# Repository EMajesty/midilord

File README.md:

# midilord

MIDI controller pedal built on ESP32-S3.

## Hardware

- 8 footswitches
- 4×40 character LCD (ST7066U, 4-bit parallel)
- 1 MIDI IN, multiple MIDI OUTs
- USB MIDI (native ESP32-S3 USB OTG port)
- 9V pedal power, regulated to 5V and 3.3V logic

### LCD pinout (XNY4004A, 18-pin)

| Pin | Function |
|-----|----------|
| 1 | DB0 |
| 2 | DB1 |
| 3 | DB2 |
| 4 | DB3 |
| 5 | DB4 |
| 6 | DB5 |
| 7 | DB6 |
| 8 | DB7 |
| 9 | E1 |
| 10 | R/W |
| 11 | RS |
| 12 | Vo (contrast) |
| 13 | VSS (GND) |
| 14 | VDD (+5V) |
| 15 | E2 |
| 16 | NC |
| 17 | Backlight + |
| 18 | Backlight - |

## Planned features

- Morningstar-inspired function set
- Presets and banks (16 banks × 8 presets)
- Tap tempo
- Web server for preset and config editing

[LCD Datasheet](https://www.crystalfontz.com/products/document/931/CFAH4004A-YYH-JTDatasheetRelease2021-11-03.pdf)
[APA106](https://cdn.sparkfun.com/datasheets/Components/LED/COM-12877.pdf)

```
x0123456789012345678901234567890123456789
0 [Preset]  [Preset]  [Preset]  [Preset]
1
2
3 [Preset]  [Preset]  [Preset]  [Preset]
```

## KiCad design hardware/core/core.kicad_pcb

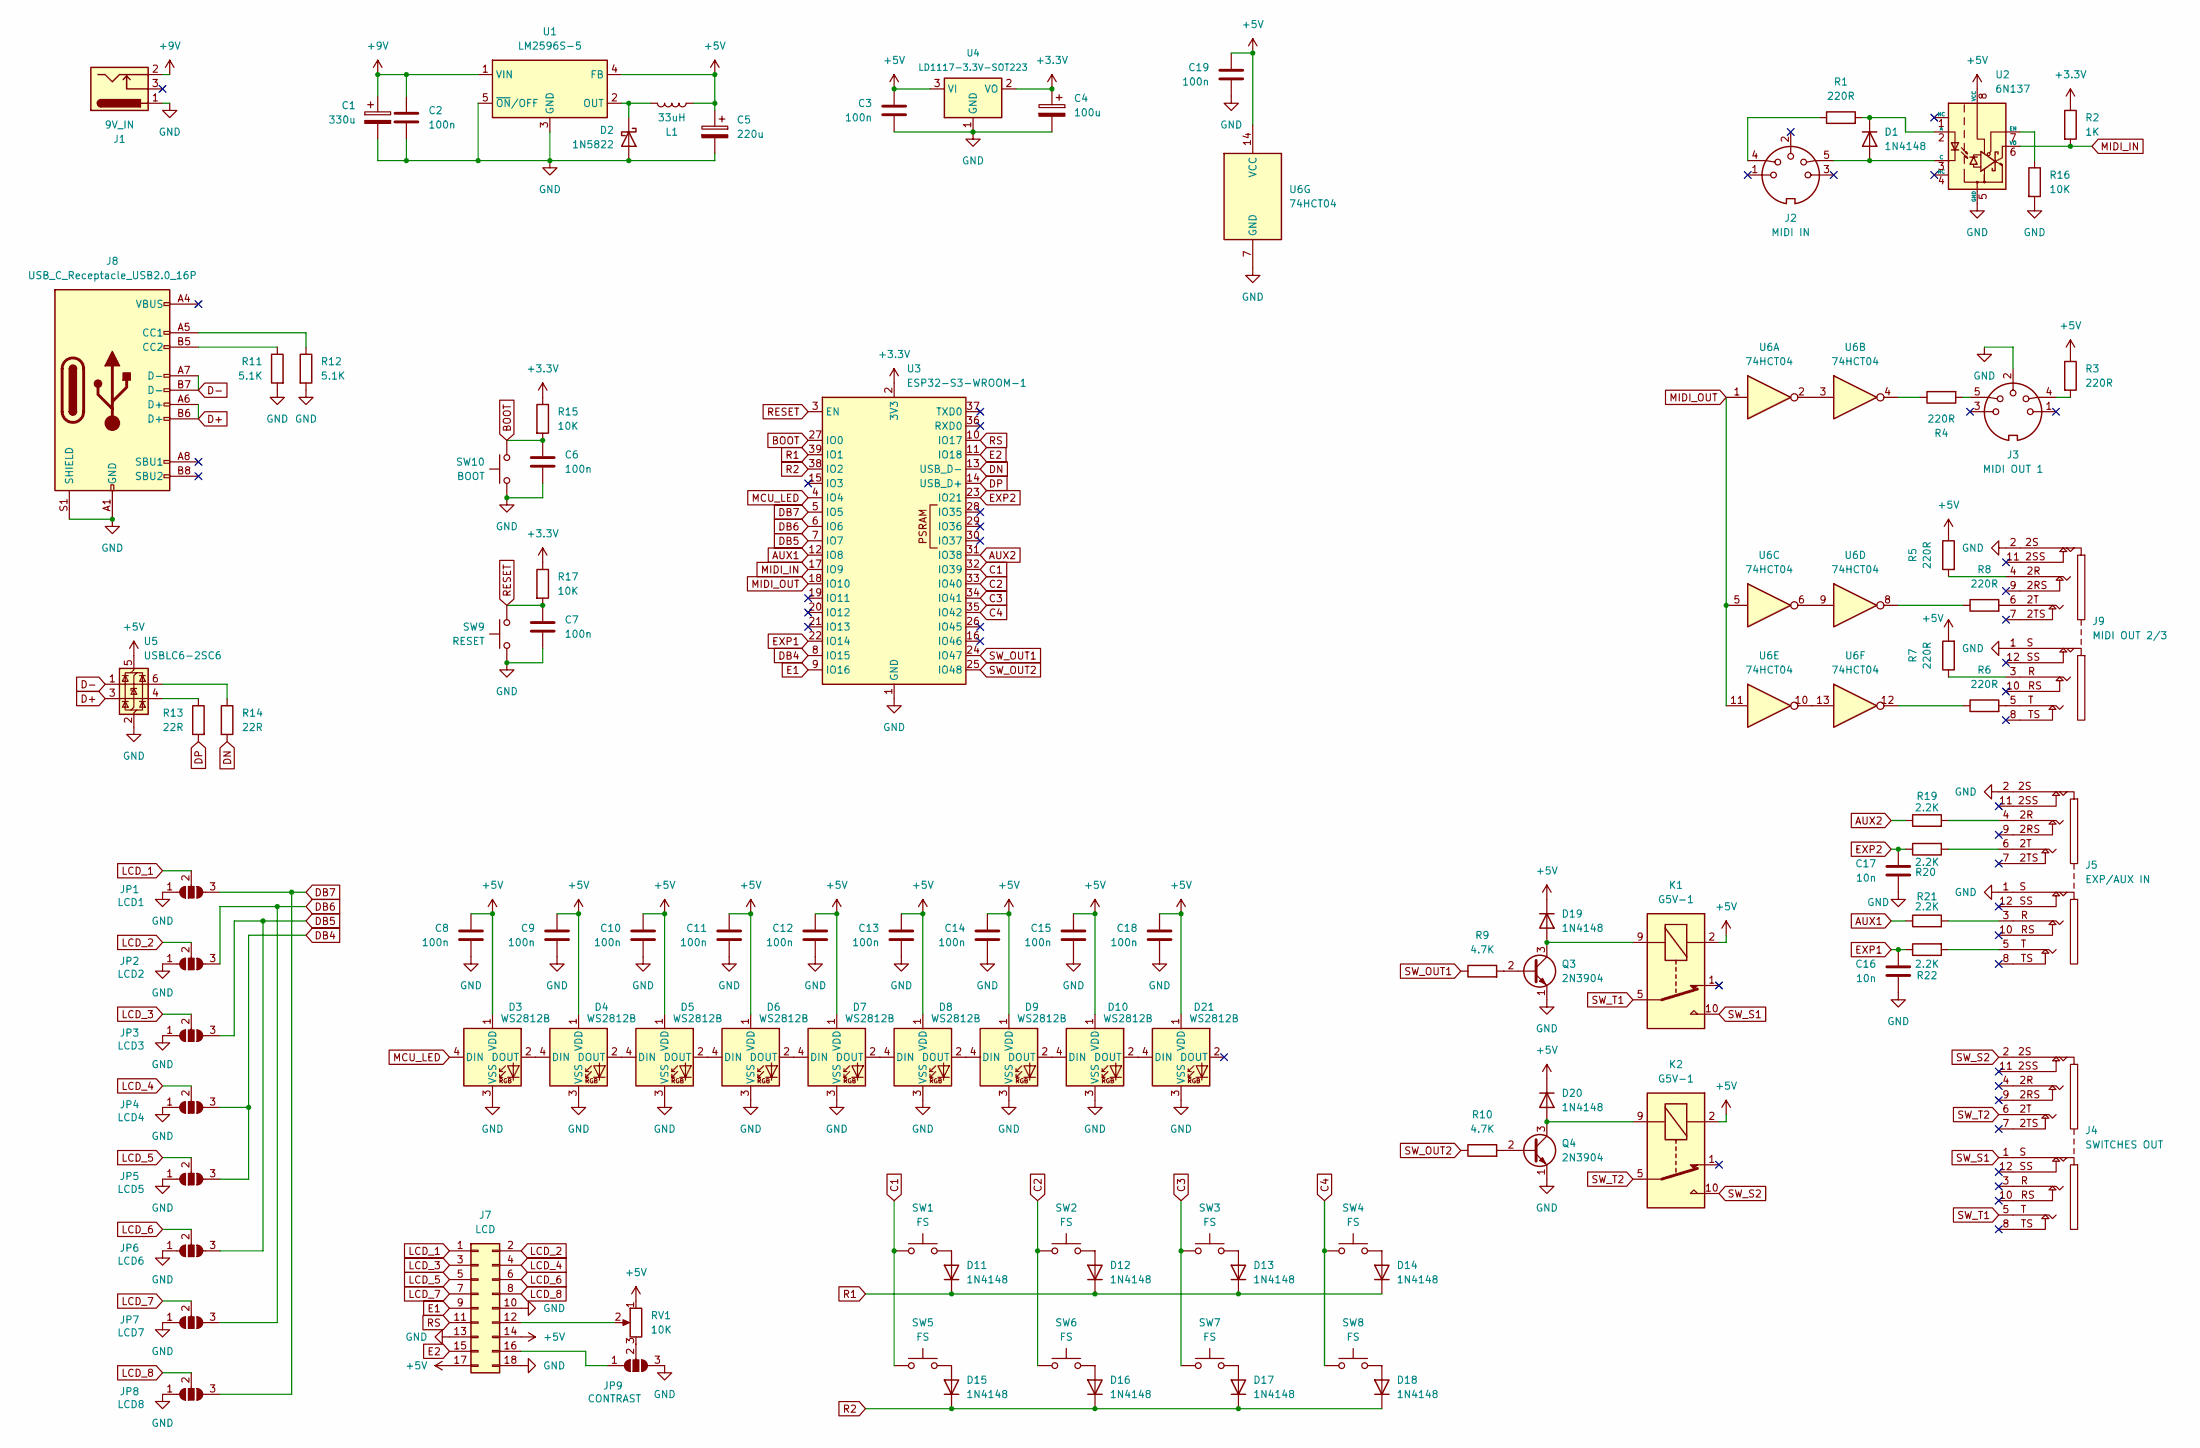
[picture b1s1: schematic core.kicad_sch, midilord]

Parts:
C1: 330u; CP_Radial_D10.0mm_P5.00mm
C2, C3, C6, C7, C8, C9, C10, C11, C12, C13, C14, C15, C18, C19: 100n; C_Rect_L7.0mm_W2.5mm_P5.00mm
C4: 100u; CP_Radial_D8.0mm_P3.50mm
C5: 220u; CP_Radial_D8.0mm_P3.50mm
C16, C17: 10n; C_Rect_L7.0mm_W2.5mm_P5.00mm
D1: 1N4148; D_DO-35_SOD27_P7.62mm_Horizontal
D2: 1N5822; D_DO-201AD_P15.24mm_Horizontal
D3, D4, D5, D6, D7, D8, D9, D10, D21: WS2812B; APA106
D11, D12, D13, D14, D15, D16, D17, D18, D19, D20: 1N4148; D_T-1_P5.08mm_Horizontal
J1: 9V_IN; BarrelJack_Horizontal
J2: MIDI IN; DIN5_180
J3: MIDI OUT 1; DIN5_180
J4: SWITCHES OUT; CK635-037
J5: EXP/AUX IN; CK635-037
J7: LCD; 4004A
J8: USB_C_Receptacle_USB2.0_16P; USB_C_Receptacle_GCT_USB4085
J9: MIDI OUT 2/3; CK635-037
JP1: LCD1; SolderJumper-3_P1.3mm_Open_RoundedPad1.0x1.5mm
JP2: LCD2; SolderJumper-3_P1.3mm_Open_RoundedPad1.0x1.5mm
JP3: LCD3; SolderJumper-3_P1.3mm_Open_RoundedPad1.0x1.5mm
JP4: LCD4; SolderJumper-3_P1.3mm_Open_RoundedPad1.0x1.5mm
JP5: LCD5; SolderJumper-3_P1.3mm_Open_RoundedPad1.0x1.5mm
JP6: LCD6; SolderJumper-3_P1.3mm_Open_RoundedPad1.0x1.5mm
JP7: LCD7; SolderJumper-3_P1.3mm_Open_RoundedPad1.0x1.5mm
JP8: LCD8; SolderJumper-3_P1.3mm_Open_RoundedPad1.0x1.5mm
JP9: CONTRAST; SolderJumper-3_P1.3mm_Open_RoundedPad1.0x1.5mm
K1, K2: G5V-1; Relay_SPDT_Omron_G5V-1
L1: 33uH; L_Radial_D9.5mm_P5.00mm_Fastron_07HVP
Q3, Q4: 2N3904; TO-92_Inline_Wide
R1, R3, R4, R5, R6, R7, R8: 220R; R_Axial_DIN0204_L3.6mm_D1.6mm_P7.62mm_Horizontal
R2: 1K; R_Axial_DIN0204_L3.6mm_D1.6mm_P7.62mm_Horizontal
R9, R10: 4.7K; R_Axial_DIN0204_L3.6mm_D1.6mm_P7.62mm_Horizontal
R11, R12: 5.1K; R_Axial_DIN0204_L3.6mm_D1.6mm_P7.62mm_Horizontal
R13, R14: 22R; R_Axial_DIN0204_L3.6mm_D1.6mm_P7.62mm_Horizontal
R15, R16, R17: 10K; R_Axial_DIN0204_L3.6mm_D1.6mm_P7.62mm_Horizontal
R19, R20, R21, R22: 2.2K; R_Axial_DIN0204_L3.6mm_D1.6mm_P7.62mm_Horizontal
RV1: 10K; Potentiometer_Bourns_3296Y_Vertical
SW1, SW2, SW3, SW4, SW5, SW6, SW7, SW8: FS; Footswitch
SW9: RESET; SW_PUSH_1P1T_6x3.5mm_H5.0_APEM_MJTP1250
SW10: BOOT; SW_PUSH_1P1T_6x3.5mm_H5.0_APEM_MJTP1250
U1: LM2596S-5; TO-263-5_TabPin3
U2: 6N137; DIP-8_W7.62mm
U3: ESP32-S3-WROOM-1
U4: LD1117-3.3V-SOT223; SOT-223; Part Number LD1117S33CTR
U5: USBLC6-2SC6; SOT-23-6
U6: 74HCT04; DIP-14_W7.62mm_Socket_LongPads

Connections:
+3.3V: C4.1, R2.1, R15.1, R17.1, U3.2 (3V3), U4.2 (VO)
+5V: C3.1, C5.1, C8.1, C9.1, C10.1, C11.1, C12.1, C13.1, C14.1, C15.1, C18.1, C19.1, D3.1 (VDD), D4.1 (VDD), D5.1 (VDD), D6.1 (VDD), D7.1 (VDD), D8.1 (VDD), D9.1 (VDD), D10.1 (VDD), D19.1 (K), D20.1 (K), D21.1 (VDD), J7.14, J7.17, K1.2, K2.2, L1.2, R3.1, R5.1, R7.2, RV1.1, U1.4 (FB), U2.8 (VCC), U4.3 (VI), U5.5 (VBUS), U6.14 (VCC)
+9V: C1.1, C2.1, J1.2, U1.1 (VIN)
AUX1: R21.1, U3.12 (IO8)
AUX2: R19.1, U3.31 (IO38)
BOOT: C6.1, R15.2, SW10.2, U3.27 (IO0)
C1: SW1.2, SW5.1, U3.32 (IO39)
C2: SW2.2, SW6.1, U3.33 (IO40)
C3: SW3.1, SW7.2, U3.34 (IO41)
C4: SW4.1, SW8.2, U3.35 (IO42)
D+: J8.A6 (D+), J8.B6 (D+), U5.3 (I/O2)
D-: J8.A7 (D-), J8.B7 (D-), U5.1 (I/O1)
DB4: JP4.3 (B), JP5.3 (B), U3.8 (IO15)
DB5: JP3.3 (B), JP6.3 (B), U3.7 (IO7)
DB6: JP2.3 (B), JP7.3 (B), U3.6 (IO6)
DB7: JP1.3 (B), JP8.3 (B), U3.5 (IO5)
DN: R14.2, U3.13 (USB_D-)
DP: R13.2, U3.14 (USB_D+)
E1: J7.9, U3.9 (IO16)
E2: J7.15, U3.11 (IO18)
EXP1: C16.1, R22.1, U3.22 (IO14)
EXP2: C17.1, R20.1, U3.23 (IO21)
GND: C1.2, C2.2, C3.2, C4.2, C5.2, C6.2, C7.2, C8.2, C9.2, C10.2, C11.2, C12.2, C13.2, C14.2, C15.2, C16.2, C17.2, C18.2, C19.2, D2.2 (A), D3.3 (VSS), D4.3 (VSS), D5.3 (VSS), D6.3 (VSS), D7.3 (VSS), D8.3 (VSS), D9.3 (VSS), D10.3 (VSS), D21.3 (VSS), J1.1, J3.2, J5.1 (S), J5.2 (2S), J7.10, J7.13, J7.18, J8.A1 (GND), J8.A12 (GND), J8.B1 (GND), J8.B12 (GND), J8.S1 (SHIELD), J9.1 (S), J9.2 (2S), JP1.1 (A), JP2.1 (A), JP3.1 (A), JP4.1 (A), JP5.1 (A), JP6.1 (A), JP7.1 (A), JP8.1 (A), JP9.3 (B), Q3.1 (E), Q4.1 (E), R11.2, R12.2, R16.2, SW9.1, SW10.1, U1.3 (GND), U1.5 (~ON/OFF), U2.5 (GND), U3.1 (GND), U3.40 (GND), U3.41 (GND), U4.1 (GND), U5.2 (GND), U6.7 (GND)
LCD_1: J7.1, JP1.2 (C)
LCD_2: J7.2, JP2.2 (C)
LCD_3: J7.3, JP3.2 (C)
LCD_4: J7.4, JP4.2 (C)
LCD_5: J7.5, JP5.2 (C)
LCD_6: J7.6, JP6.2 (C)
LCD_7: J7.7, JP7.2 (C)
LCD_8: J7.8, JP8.2 (C)
MCU_LED: D3.4 (DIN), U3.4 (IO4)
MIDI_IN: R2.2, U2.6 (VO), U3.17 (IO9)
MIDI_OUT: U3.18 (IO10), U6.1, U6.5, U6.11
unnamed: D1.2 (A), J2.5, U2.3 (C)
unnamed: D1.1 (K), R1.2, U2.2 (A)
unnamed: D2.1 (K), L1.1, U1.2 (OUT)
unnamed: D3.2 (DOUT), D4.4 (DIN)
unnamed: D4.2 (DOUT), D5.4 (DIN)
unnamed: D5.2 (DOUT), D6.4 (DIN)
unnamed: D6.2 (DOUT), D7.4 (DIN)
unnamed: D7.2 (DOUT), D8.4 (DIN)
unnamed: D8.2 (DOUT), D9.4 (DIN)
unnamed: D9.2 (DOUT), D10.4 (DIN)
unnamed: D10.2 (DOUT), D21.4 (DIN)
unnamed: D11.2 (A), SW1.1
unnamed: D12.2 (A), SW2.1
unnamed: D13.2 (A), SW3.2
unnamed: D14.2 (A), SW4.2
unnamed: D15.2 (A), SW5.2
unnamed: D16.2 (A), SW6.2
unnamed: D17.2 (A), SW7.1
unnamed: D18.2 (A), SW8.1
unnamed: D19.2 (A), K1.9, Q3.3 (C)
unnamed: D20.2 (A), K2.9, Q4.3 (C)
unnamed: J2.4, R1.1
unnamed: J3.4, R3.2
unnamed: J3.5, R4.2
unnamed: J5.4 (2R), R19.2
unnamed: J5.6 (2T), R20.2
unnamed: J5.3 (R), R21.2
unnamed: J5.5 (T), R22.2
unnamed: J7.12, RV1.2
unnamed: J7.16, JP9.1 (A)
unnamed: J8.A5 (CC1), R12.1
unnamed: J8.B5 (CC2), R11.1
unnamed: J9.4 (2R), R5.2
unnamed: J9.6 (2T), R8.2
unnamed: J9.3 (R), R7.1
unnamed: J9.5 (T), R6.2
unnamed: JP9.2 (C), RV1.3
unnamed: Q3.2 (B), R9.2
unnamed: Q4.2 (B), R10.2
unnamed: R4.1, U6.4
unnamed: R6.1, U6.12
unnamed: R8.1, U6.8
unnamed: R13.1, U5.4 (I/O2)
unnamed: R14.1, U5.6 (I/O1)
unnamed: R16.1, U2.7 (EN)
unnamed: U6.2, U6.3
unnamed: U6.6, U6.9
unnamed: U6.10, U6.13
R1: D11.1 (K), D12.1 (K), D13.1 (K), D14.1 (K), U3.39 (IO1)
R2: D15.1 (K), D16.1 (K), D17.1 (K), D18.1 (K), U3.38 (IO2)
RESET: C7.1, R17.2, SW9.2, U3.3 (EN)
RS: J7.11, U3.10 (IO17)
SW_OUT1: R9.1, U3.24 (IO47)
SW_OUT2: R10.1, U3.25 (IO48)
SW_S1: J4.1 (S), K1.10
SW_S2: J4.2 (2S), K2.10
SW_T1: J4.5 (T), K1.5, K1.6
SW_T2: J4.6 (2T), K2.5, K2.6

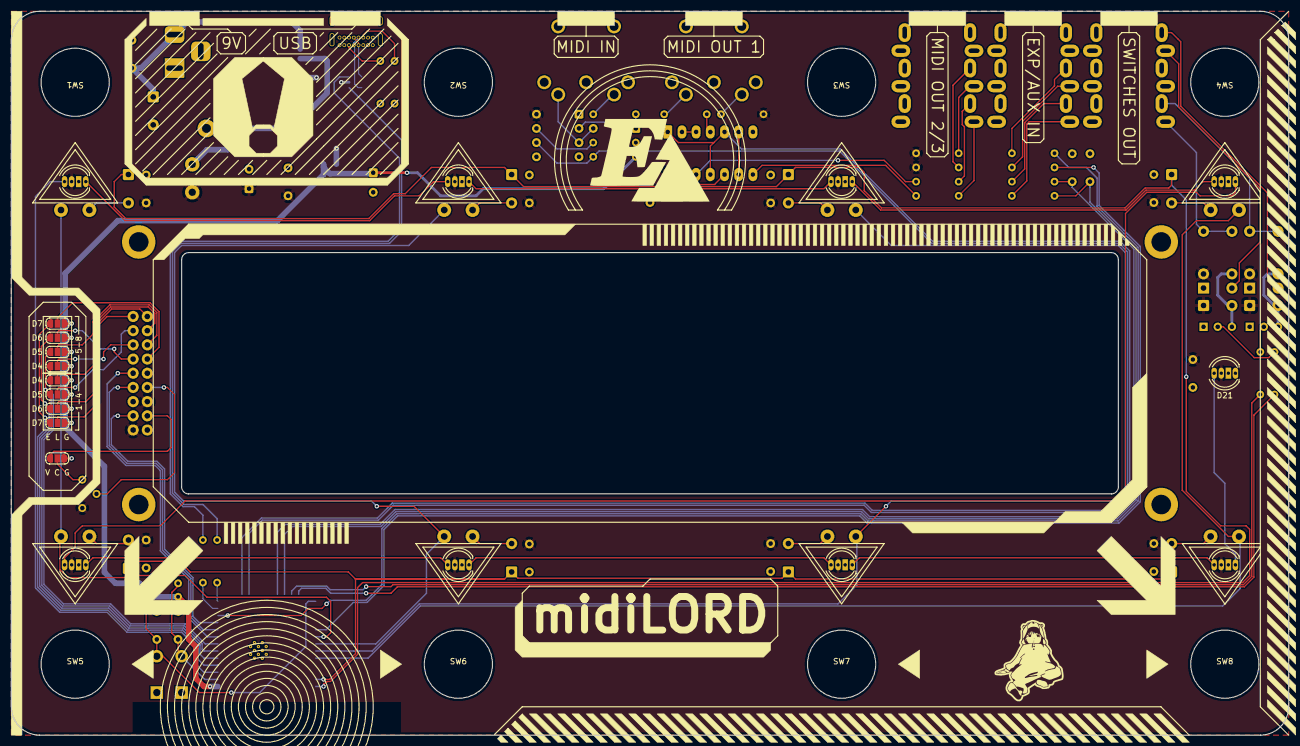
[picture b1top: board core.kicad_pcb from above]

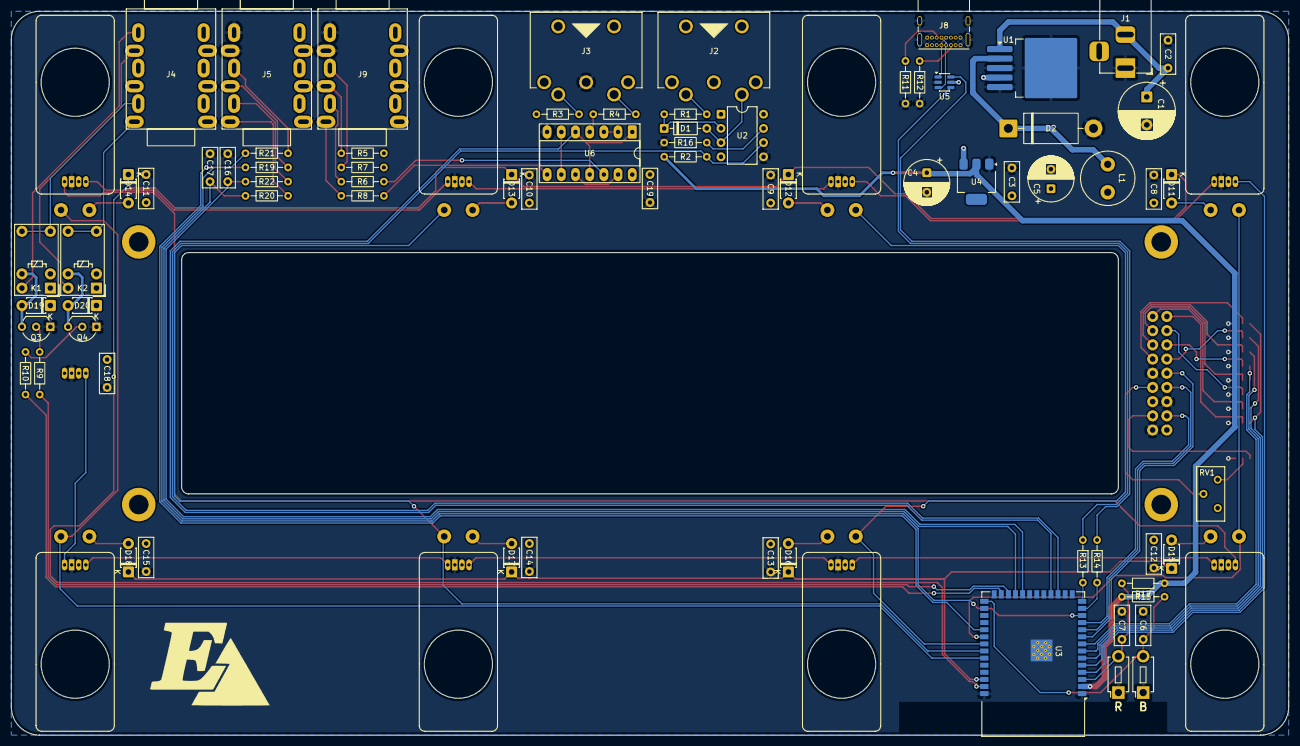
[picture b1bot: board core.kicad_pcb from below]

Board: 2 copper layers, 228.6 x 129.5 mm, 100 parts (73 on the bottom side), 92 nets.

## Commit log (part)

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2024-07-10 screen test
2024-07-10 screen work
2024-07-11 wiring revision
2024-07-12 midi
2024-07-13 switches work, library change
2024-07-13 midi output works, begun data structure
2024-08-12 persistent storage working
2024-08-12 saving banks to flash implemented, started sysex sending
2024-08-13 asdfasdf
2024-08-14 big stuff
2024-08-14 compiledb to root, lsp works
2024-08-14 basic sending and receiving of sysex
2024-08-14 some sysex handling
2024-08-23 disable waiting for usb mounting
2024-08-25 code cleanup / separate into multiple files
2024-08-25 more cleanup
2024-08-26 splitting headers to sources
2024-09-01 preset to sendable array
2024-09-01 fix lcd preset name writing pos
2024-09-01 initialized message memory
2025-08-16 add pcb files, reorganize
2025-08-17 pcb proge
2026-05-04 Reorganize repo: add README, remove firmware and pcb files
2026-05-26 Prompt is too long
2026-05-30 Reduce PCB to 2-layer stackup and update design rules
2026-05-30 Add PCB/schematic PDFs and hardware bitmap asset
2026-05-31 Add clangd index cache for firmware dependencies
2026-05-31 Remove clangd index cache from version control
2026-05-31 Add WS2812B LED support, update LCD pinout docs, and revise PCB nets
2026-05-31 Add APA106 LED datasheet link to README
2026-05-31 Update power spec to include 5V regulation stage
2026-06-01 Add EMaj logo SVG and silkscreen artwork to PCB
2026-06-01 Add LCD preset layout diagram and DIN5-180 connector 3D model
2026-06-01 Add LCD and LED driver modules, refactor main.cpp
2026-06-02 Add vegas mode stubs and update LED count to 8
2026-06-04 Reposition silkscreen logos, add mounting hole circles, remove channel number labels
2026-06-04 Adjust connector positions and reroute nearby traces
2026-06-04 Move footswitch silkscreen circle to Dwgs.User layer
2026-06-05 Add event system, switch matrix, MIDI outputs, and LED helpers
2026-06-05 Replace footswitch connector nets with aux/expression nets and renumber
2026-06-07 Add storage, midiport, and types modules; refactor event system
2026-06-09 Add LittleFS bank storage, enable MIDI ports, and split LED clear/set
2026-06-09 Implement MIDI CC and PC message sending on both ports
2026-06-09 Update PCB layout with revised nets and add D21 WS2812B LED
2026-06-09 API Error: 500 {"type":"error","error":{"type":"api_error","message":"Internal server error"},"request_id":"req_011Cbt6DiXSF9rwzrKTGDxFn"}
2026-06-09 Convert char key to integer using atoi in keypad press handler
2026-06-16 Add LCD bank/preset display and bank navigation
2026-06-16 Fix LCD preset layout indexing and remove unused test functions
2026-06-16 Update PCB layout and fix DRC warnings for unconnected pins
2026-06-22 Move header files to firmware/inc and add include path
